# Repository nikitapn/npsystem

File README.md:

# npsystem

A DCS system built around 8-bit AVR micro controller.

## Key Features
- Multi master protocol loosely based on P-NET
- Control units can be uploaded on the fly
- Modify and see propagation of the signal on the running algorithms
- Signal quality bit propagation
- Each micro contoller is an independet unit which can send requests to other devices on the network
- Logic can be tested on virtual controlles
- Controllers supports integration with custom modules via I2C and memory addresses mapping

## Dependencies on Windows
- cygwin https://www.cygwin.com
- make https://gnuwin32.sourceforge.net/packages/make.htm
- perl https://strawberryperl.com
- boost https://www.boost.org/
- leveldb https://github.com/google/leveldb
- scintilla https://www.scintilla.org/SciTEDownload.html
- wtl https://wtl.sourceforge.io/
- AVR toolchain https://www.microchip.com/en-us/tools-resources/develop/microchip-studio/gcc-compilers
- avrdude https://www.nongnu.org/avrdude

## Pictures

<p align="center">
  <b>How it looks</b>
  
  <b>Structural Diagram</b>
  
</p>

## TODO
- [ ] A proper compiler based on LLVM, maybe? With a support for ST language and quality bit propagation.
- [ ] Probably need to remove bit values. It's hard to deal with.
- [ ] Sort dependencies and load all algorithm at once.
- [ ] Add more tests.
- [ ] Add another more powerfull MC, maybe SBP based on Linux (probably a driver will be required for the protocol).
- [ ] Add more FBD blocks (structured text block, etc...).
- [ ] Add SFC language support

## References
1. [MAX3082 Transcievers [PDF]](https://www.analog.com/media/jp/technical-documentation/data-sheets/1522.pdf)
2. [Detection of RS-485 signal loss [PDF]](https://www.ti.com/lit/an/slyt257/slyt257.pdf?ts=1746389303529&ref_url=https%253A%252F%252Fwww.google.com%252F)
3. [P-NET [PDF]](https://www.p-net.org/old/download/mctext.pdf)

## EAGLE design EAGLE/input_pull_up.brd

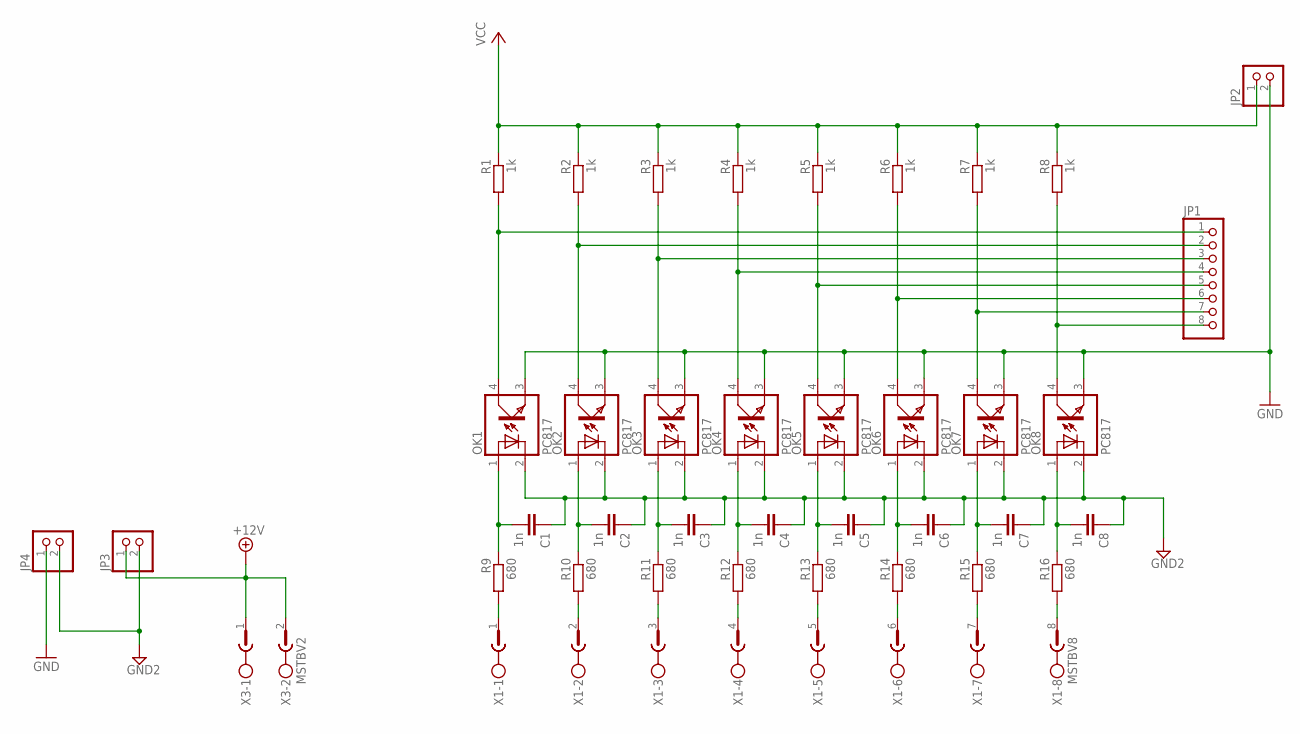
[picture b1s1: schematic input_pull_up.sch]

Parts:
C1, C2, C3, C4, C5, C6, C7, C8: 1n; C050-025X075
JP1: PINHD-1X8; 1X08
JP2, JP3, JP4: PINHD-1X2; 1X02
OK1, OK2, OK3, OK4, OK5, OK6, OK7, OK8: PC817; DIL04
R1, R2, R3, R4, R5, R6, R7, R8: 1k; 0204/7
R9, R10, R11, R12, R13, R14, R15, R16: 680; 0204/7
X1: MSTBV8
X3: MSTBV2

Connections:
+12V: JP3.1, X3.1, X3.2
GND: JP2.2, JP4.1, OK1.3 (EMIT), OK2.3 (EMIT), OK3.3 (EMIT), OK4.3 (EMIT), OK5.3 (EMIT), OK6.3 (EMIT), OK7.3 (EMIT), OK8.3 (EMIT)
GND2: C1.1, C2.1, C3.1, C4.1, C5.1, C6.1, C7.1, C8.1, JP3.2, JP4.2, OK1.2 (C), OK2.2 (C), OK3.2 (C), OK4.2 (C), OK5.2 (C), OK6.2 (C), OK7.2 (C), OK8.2 (C)
unnamed: JP1.1, OK1.4 (COL), R1.2
unnamed: JP1.2, OK2.4 (COL), R2.2
unnamed: JP1.3, OK3.4 (COL), R3.2
unnamed: JP1.4, OK4.4 (COL), R4.2
unnamed: JP1.5, OK5.4 (COL), R5.2
unnamed: JP1.6, OK6.4 (COL), R6.2
unnamed: JP1.7, OK7.4 (COL), R7.2
unnamed: JP1.8, OK8.4 (COL), R8.2
unnamed: R9.2, X1.1
unnamed: R10.2, X1.2
unnamed: R11.2, X1.3
unnamed: R12.2, X1.4
unnamed: R13.2, X1.5
unnamed: R14.2, X1.6
unnamed: R15.2, X1.7
unnamed: R16.2, X1.8
unnamed: C1.2, OK1.1 (A), R9.1
unnamed: C2.2, OK2.1 (A), R10.1
unnamed: C3.2, OK3.1 (A), R11.1
unnamed: C4.2, OK4.1 (A), R12.1
unnamed: C5.2, OK5.1 (A), R13.1
unnamed: C6.2, OK6.1 (A), R14.1
unnamed: C7.2, OK7.1 (A), R15.1
unnamed: C8.2, OK8.1 (A), R16.1
VCC: JP2.1, R1.1, R2.1, R3.1, R4.1, R5.1, R6.1, R7.1, R8.1

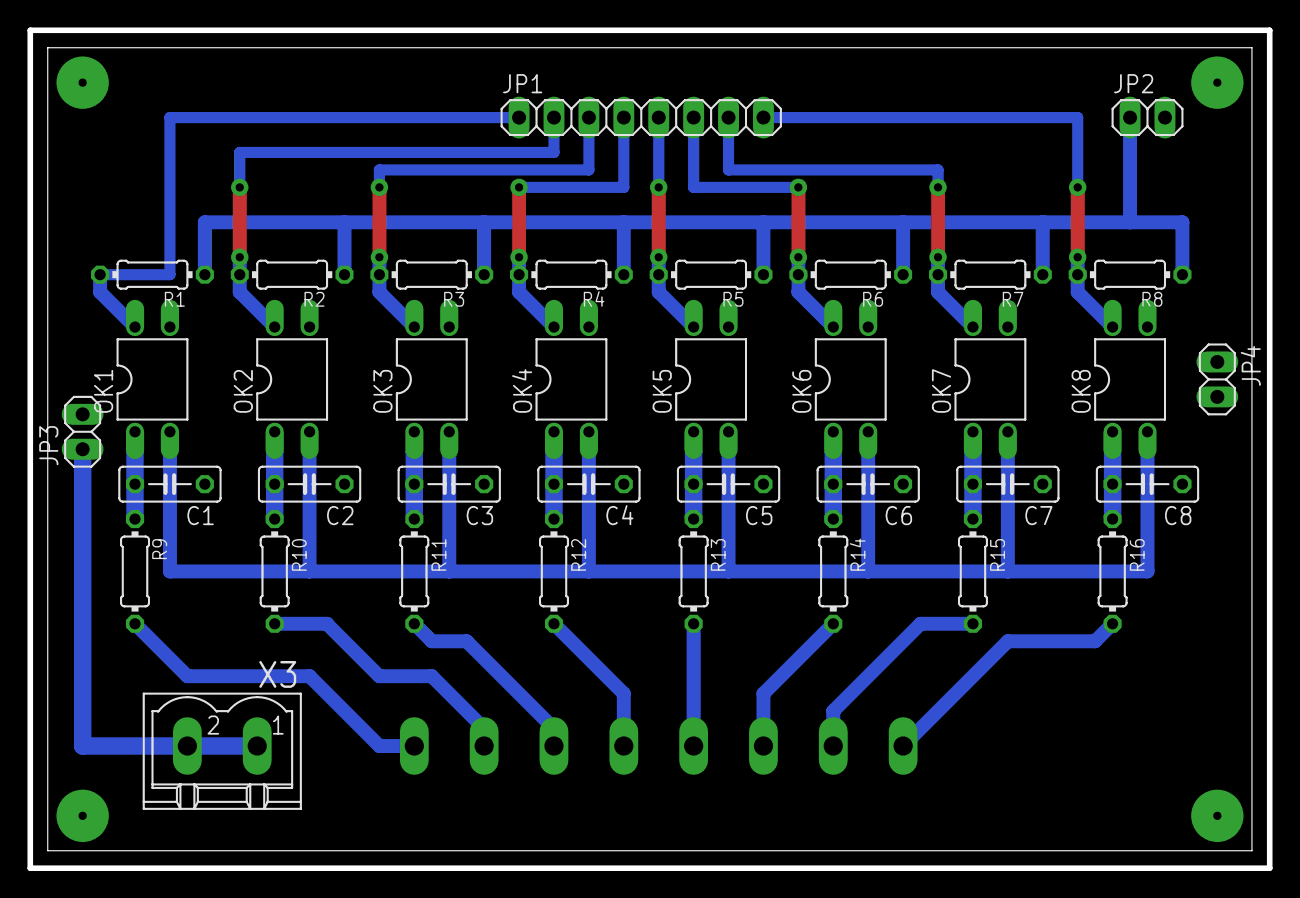
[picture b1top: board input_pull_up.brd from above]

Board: 2 copper layers, 90.2 x 61.0 mm, 38 parts (1 on the bottom side), 28 nets.

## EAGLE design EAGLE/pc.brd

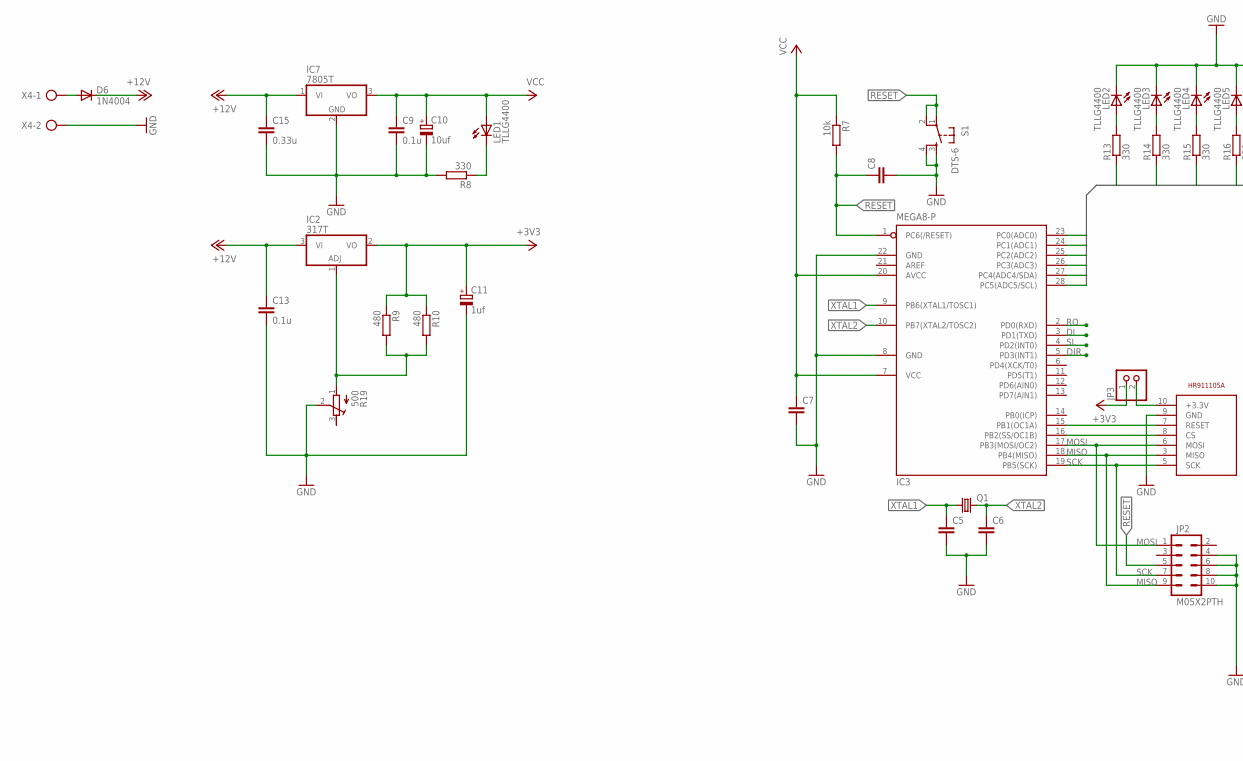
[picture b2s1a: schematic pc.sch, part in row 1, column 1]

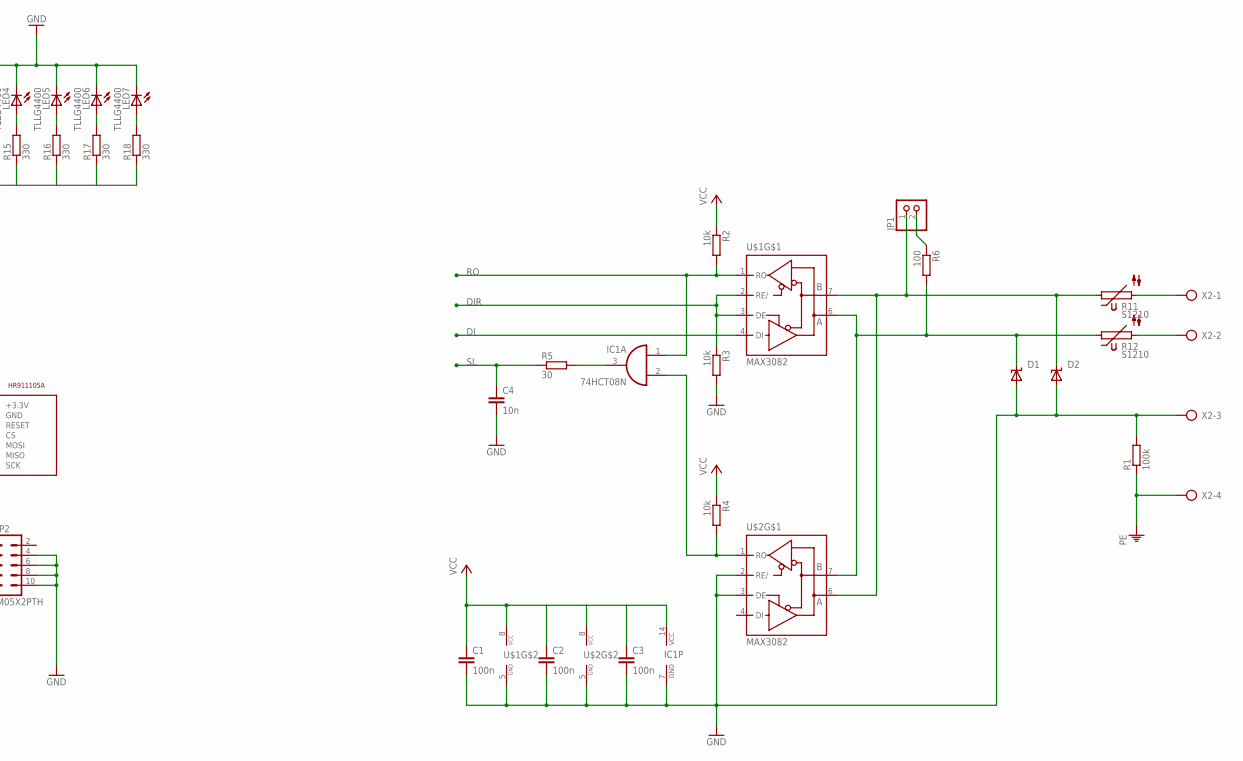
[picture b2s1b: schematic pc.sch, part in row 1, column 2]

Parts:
C1, C2, C3: 100n; C050-035X075
C4: 10n; C050-035X075
C5, C6: C-EU050-024X044; C050-024X044
C7, C8: C-EU050-025X075; C050-025X075
C9, C13: 0.1u; C025-024X044
C10: 10uf; E2-4
C11: 1uf; E2-4
C15: 0.33u; C025-024X044
D1, D2: SUPPRESSOR-SMBJ; SMBJ
D6: 1N4004; DO41-10
IC1: 74HCT08N; DIL14
IC2: 317T; TO220H
IC3: MEGA8-P; DIL28-3
IC7: 7805T; TO220H
JP1, JP3: PINHD-1X2; 1X02
JP2: M05X2PTH; AVR_ICSP
LED1, LED2, LED3, LED4, LED5, LED6, LED7: TLLG4400; LED3MM
Q1: CRYSTALHC49U70; HC49U70
R1: 100k; 0204/7
R2, R3, R4, R7: 10k; 0204/7
R5: 30; 0207/10
R6: 100; 0204/7
R8, R13, R14, R15, R16, R17, R18: 330; 0204/7
R9, R10: 480; 0204/7
R11, R12: S1210
R19: 500; RTRIM64W
S1: DTS-6
U$1, U$2: MAX3082; DIL08
U$3: HR911105A
X2: AK500/4
X4: AK500/2-H

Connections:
+3V3: C11.+, IC2.2 (VO), JP3.1, R9.1, R10.1
+12V: C13.1, C15.1, D6.C, IC2.3 (VI), IC7.1 (VI)
DI: IC3.3 (PD1(TXD)), U$1.4 (DI)
DIR: IC3.5 (PD3(INT1)), R3.1, U$1.2 (RE/), U$1.3 (DE)
GND: C1.2, C2.2, C3.2, C4.2, C5.2, C6.2, C7.2, C8.2, C9.2, C10.-, C11.-, C13.2, C15.2, D1.A, D2.A, IC1.7 (GND), IC3.8 (GND), IC3.22 (GND), IC7.2 (GND), JP2.4, JP2.6, JP2.8, JP2.10, LED2.K (C), LED3.K (C), LED4.K (C), LED5.K (C), LED6.K (C), LED7.K (C), R1.2, R3.2, R8.2, R19.2 (S), S1.3, S1.4, U$1.5 (GND), U$2.2 (RE/), U$2.3 (DE), U$2.5 (GND), U$3.9 (GND), X2.3, X4.2
LED0: IC3.23 (PC0(ADC0)), R13.1
LED1: IC3.24 (PC1(ADC1)), R14.1
LED2: IC3.25 (PC2(ADC2)), R15.1
LED3: IC3.26 (PC3(ADC3)), R16.1
LED4: IC3.27 (PC4(ADC4/SDA)), R17.1
LED5: IC3.28 (PC5(ADC5/SCL)), R18.1
MISO: IC3.18 (PB4(MISO)), JP2.9, U$3.3 (MISO)
MOSI: IC3.17 (PB3(MOSI/OC2)), JP2.1, U$3.6 (MOSI)
unnamed: IC2.1 (ADJ), R9.2, R10.2, R19.1 (A)
unnamed: D1.C, R6.2, R12.1, U$1.6 (A), U$2.7 (B)
unnamed: IC1.2 (I1), R4.2, U$2.1 (RO)
unnamed: LED1.K (C), R8.1
unnamed: IC3.16 (PB2(SS/OC1B)), U$3.8 (CS)
unnamed: LED2.A, R13.2
unnamed: IC1.3 (O), R5.2
unnamed: JP1.2, R6.1
unnamed: R11.2, X2.1
unnamed: D2.C, JP1.1, R11.1, U$1.7 (B), U$2.6 (A)
unnamed: R12.2, X2.2
unnamed: LED3.A, R14.2
unnamed: LED4.A, R15.2
unnamed: LED5.A, R16.2
unnamed: LED6.A, R17.2
unnamed: LED7.A, R18.2
unnamed: IC3.15 (PB1(OC1A)), U$3.7 (RESET)
unnamed: JP3.2, U$3.10 (+3.3V)
unnamed: D6.A, X4.1
PE: R1.1, X2.4
RESET: C8.1, IC3.1 (PC6(/RESET)), JP2.5, R7.2, S1.1, S1.2
RO: IC1.1 (I0), IC3.2 (PD0(RXD)), R2.2, U$1.1 (RO)
SCK: IC3.19 (PB5(SCK)), JP2.7, U$3.5 (SCK)
SL: C4.1, IC3.4 (PD2(INT0)), R5.1
VCC: C1.1, C2.1, C3.1, C7.1, C9.1, C10.+, IC1.14 (VCC), IC3.7 (VCC), IC3.20 (AVCC), IC7.3 (VO), LED1.A, R2.1, R4.1, R7.1, U$1.8 (VCC), U$2.8 (VCC)
XTAL1: C5.1, IC3.9 (PB6(XTAL1/TOSC1)), Q1.1
XTAL2: C6.1, IC3.10 (PB7(XTAL2/TOSC2)), Q1.2

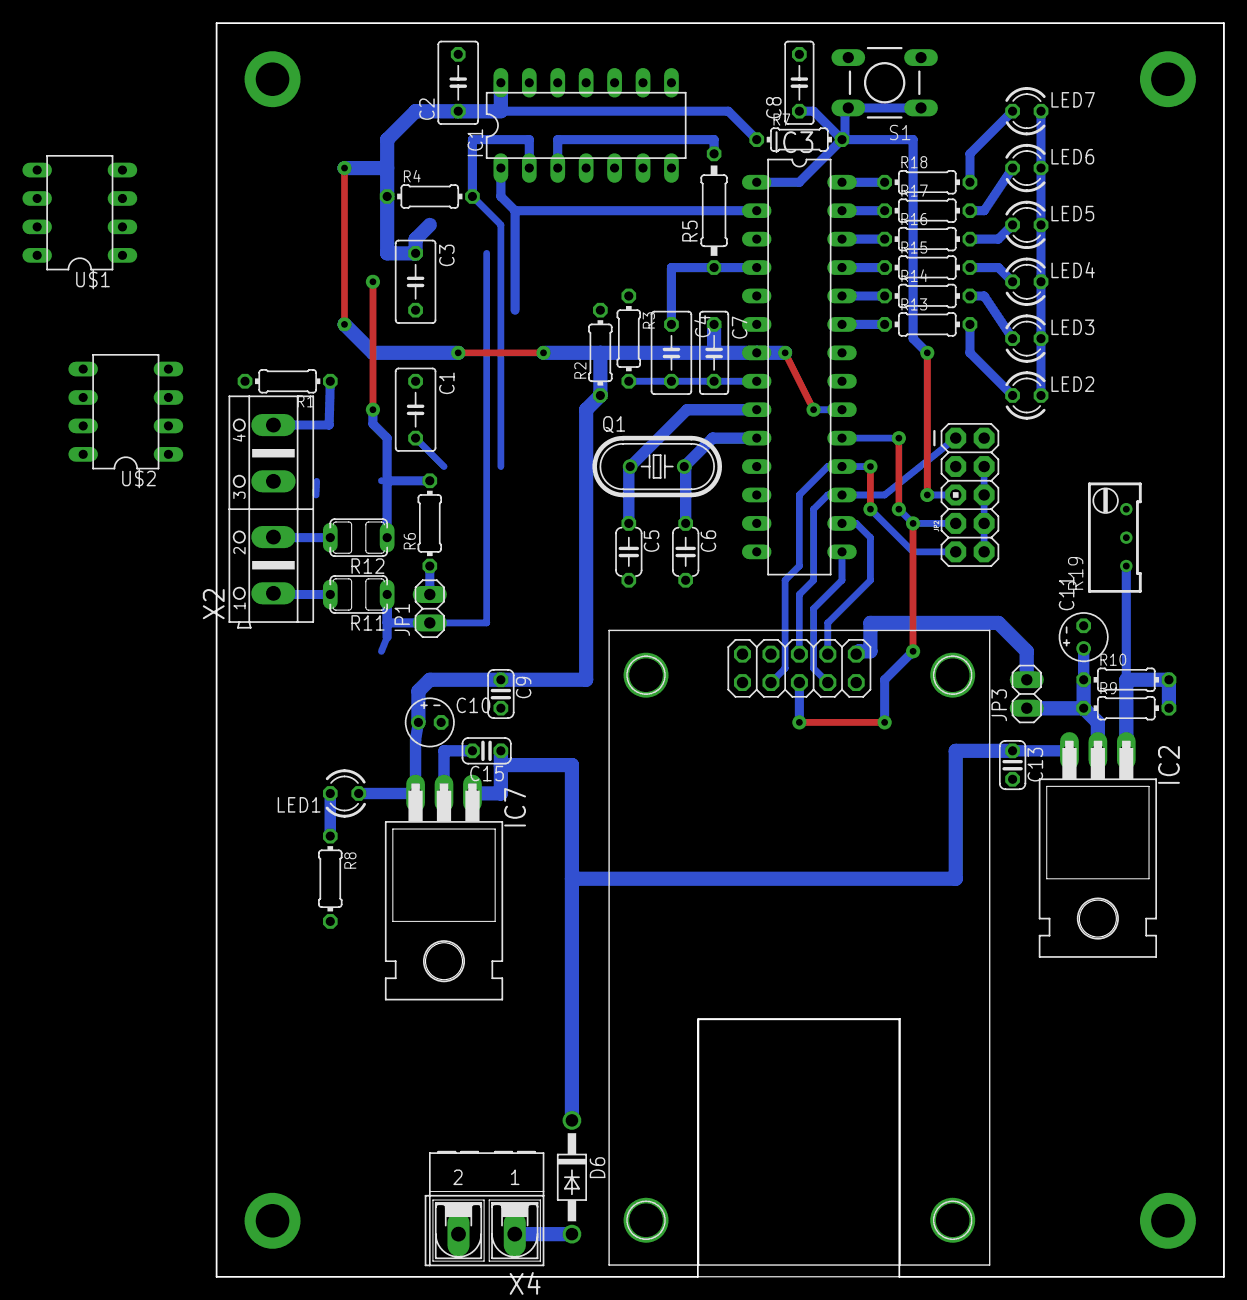
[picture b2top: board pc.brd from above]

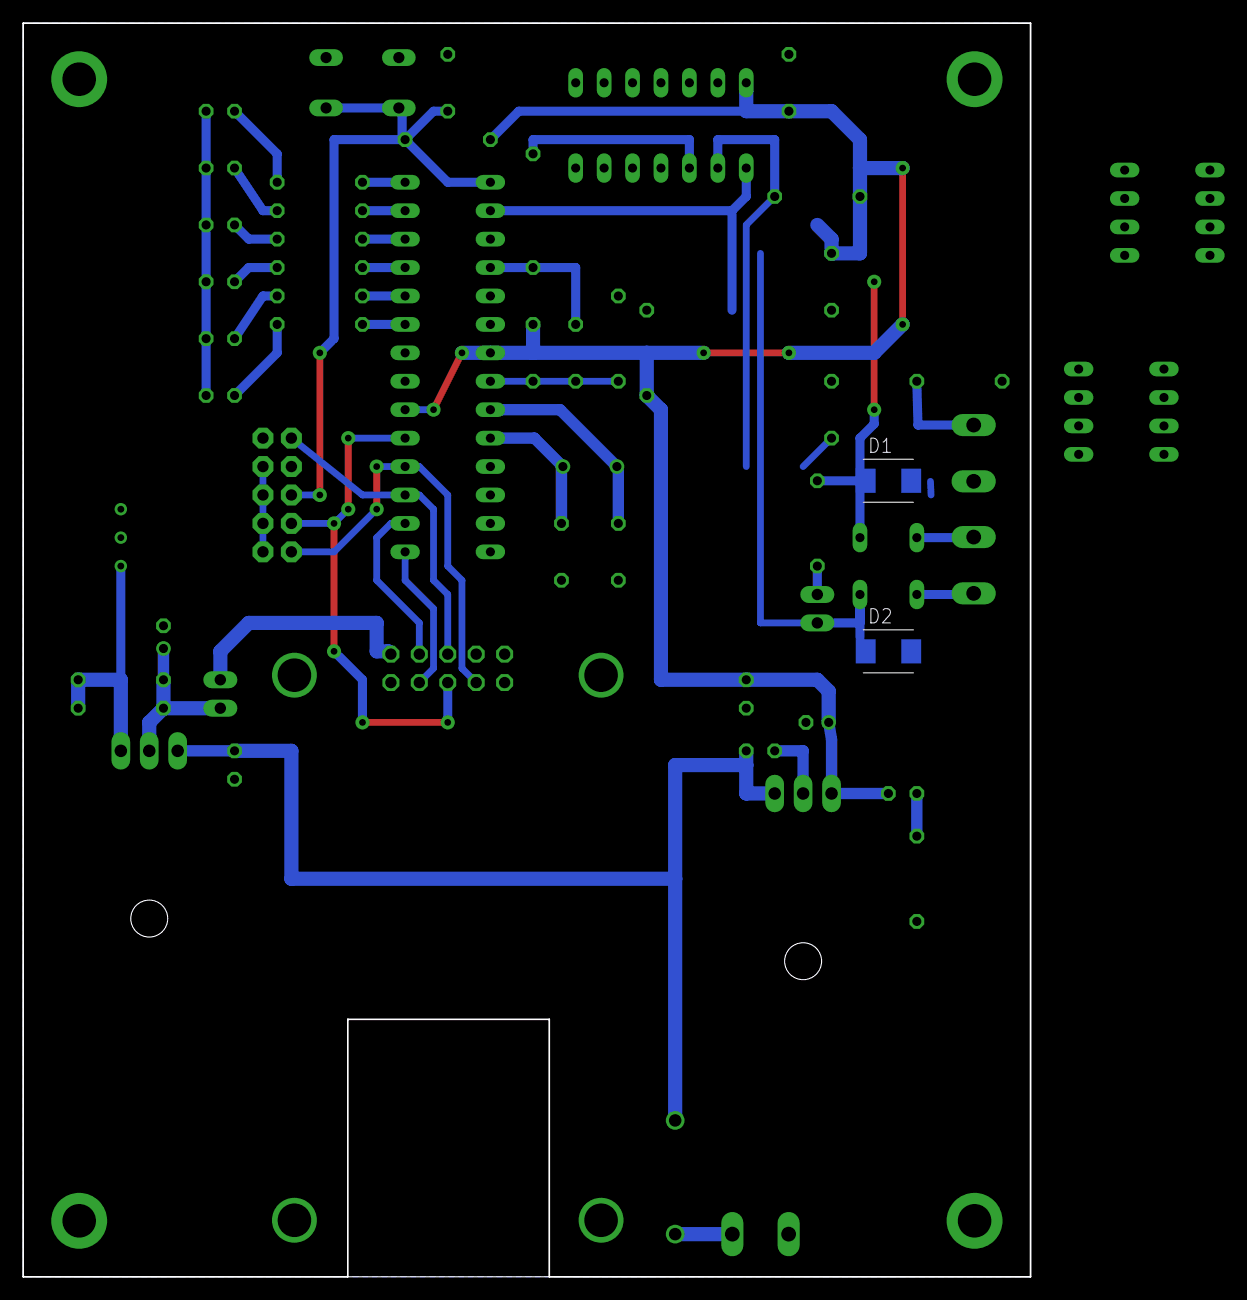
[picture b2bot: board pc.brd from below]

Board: 2 copper layers, 90.0 x 112.0 mm, 56 parts (2 on the bottom side), 40 nets.

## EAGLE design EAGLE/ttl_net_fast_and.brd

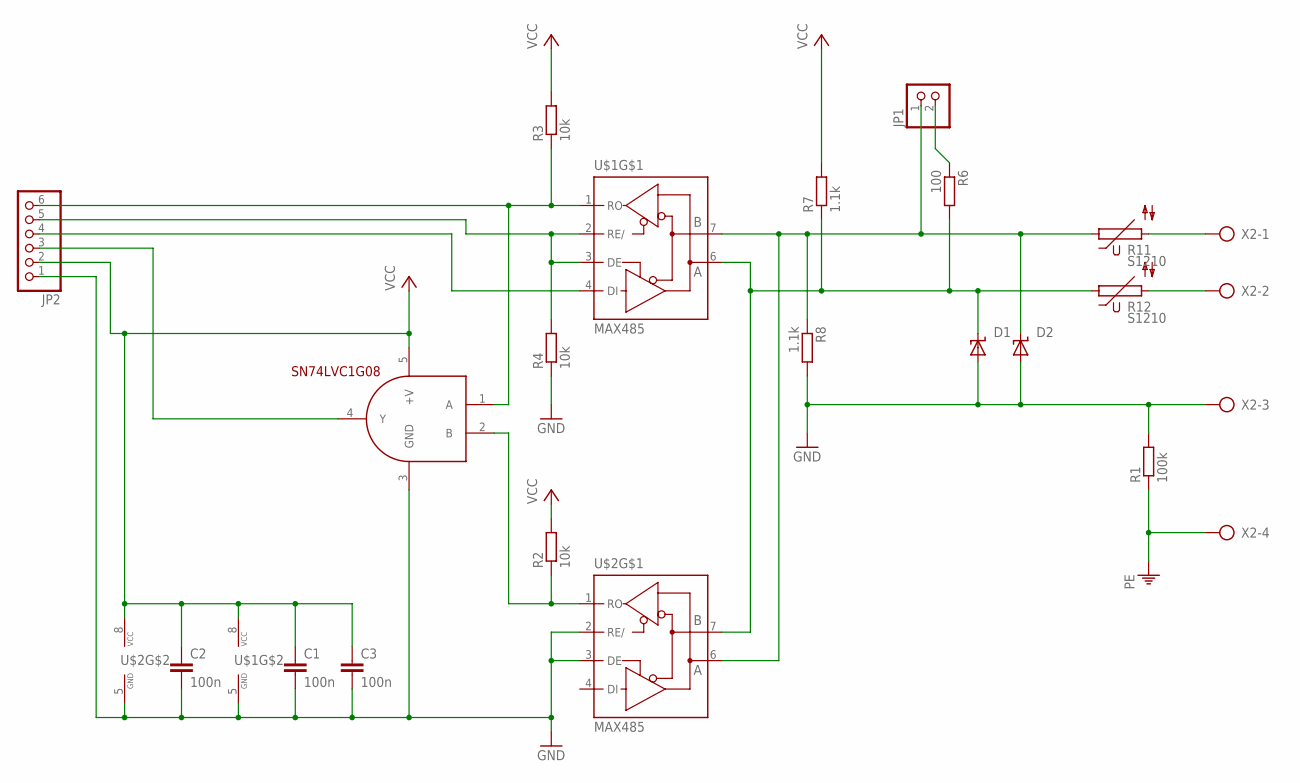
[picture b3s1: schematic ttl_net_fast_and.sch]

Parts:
C1, C2: 100n; C050-035X075
C3: 100n; C1206
D1, D2: SUPPRESSOR-SMBJ; SMBJ
JP1: PINHD-1X2; 1X02
JP2: PINHD-1X6; 1X06
R1: 100k; 0204/7
R2, R3, R4: 10k; R1206
R6: 100; 0204/7
R7, R8: 1.1k; 0204/7
R11, R12: S1210
U$1, U$2: MAX485; DIL08
U$3: SN74LVC1G08; SOT23-5
X2: AK500/4

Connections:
GND: C1.2, C2.2, C3.2, D1.A, D2.A, JP2.1, R1.2, R4.1, R8.2, U$1.5 (GND), U$2.2 (RE/), U$2.3 (DE), U$2.5 (GND), U$3.3 (GND), X2.3
unnamed: D1.C, R6.2, R7.1, R12.1, U$1.6 (A), U$2.7 (B)
unnamed: R2.1, U$2.1 (RO), U$3.2 (B)
unnamed: JP2.4, U$1.4 (DI)
unnamed: JP2.3, U$3.4 (Y)
unnamed: JP2.6, R3.1, U$1.1 (RO), U$3.1 (A)
unnamed: JP2.5, R4.2, U$1.2 (RE/), U$1.3 (DE)
unnamed: JP1.2, R6.1
unnamed: R11.2, X2.1
unnamed: D2.C, JP1.1, R8.1, R11.1, U$1.7 (B), U$2.6 (A)
unnamed: R12.2, X2.2
PE: R1.1, X2.4
VCC: C1.1, C2.1, C3.1, JP2.2, R2.2, R3.2, R7.2, U$1.8 (VCC), U$2.8 (VCC), U$3.5 (+V)

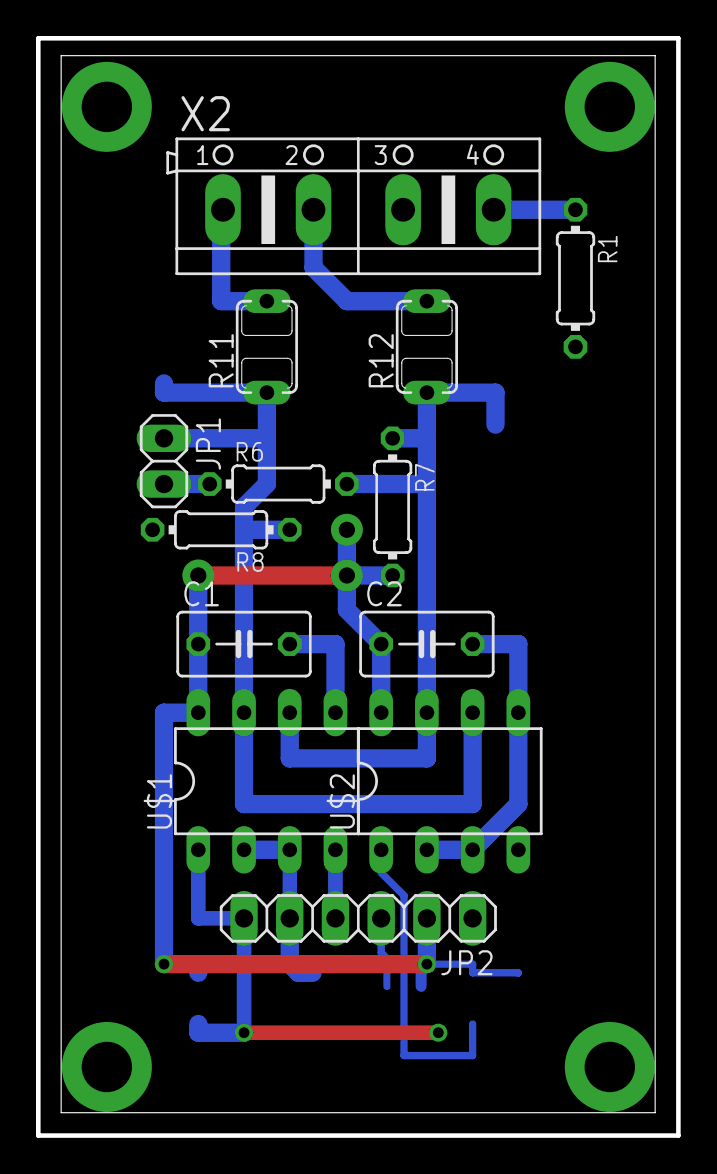
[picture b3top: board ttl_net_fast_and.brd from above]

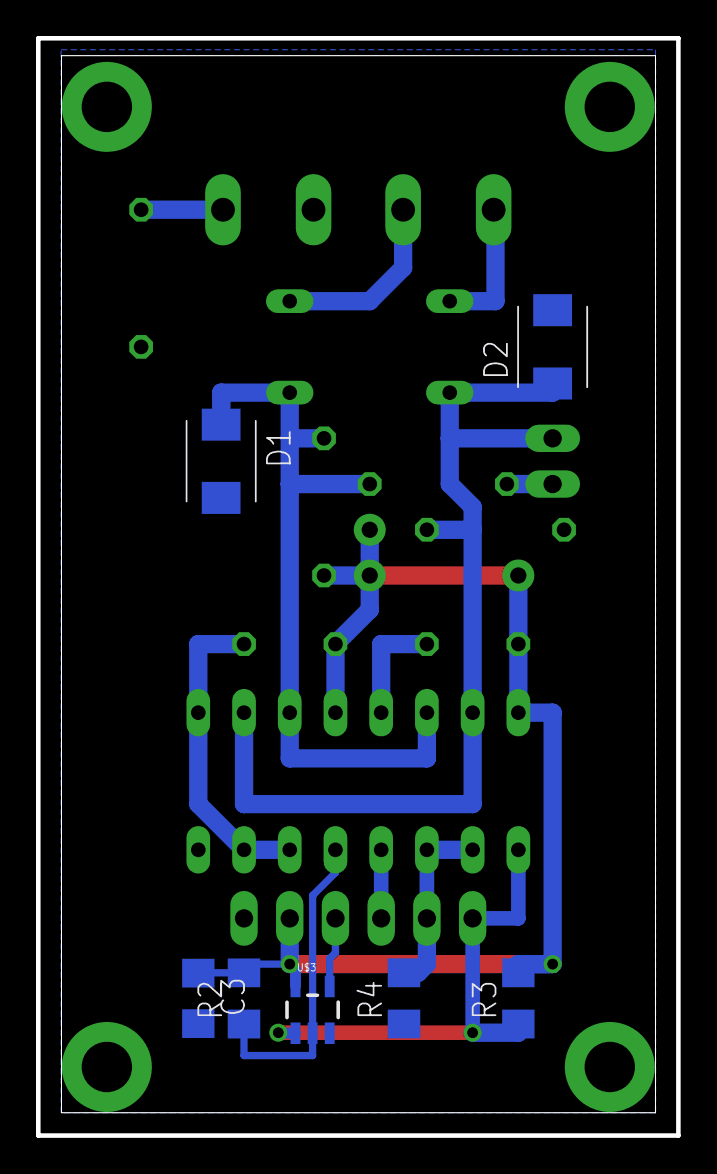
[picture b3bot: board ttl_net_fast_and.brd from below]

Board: 2 copper layers, 35.6 x 61.0 mm, 20 parts (7 on the bottom side), 13 nets.

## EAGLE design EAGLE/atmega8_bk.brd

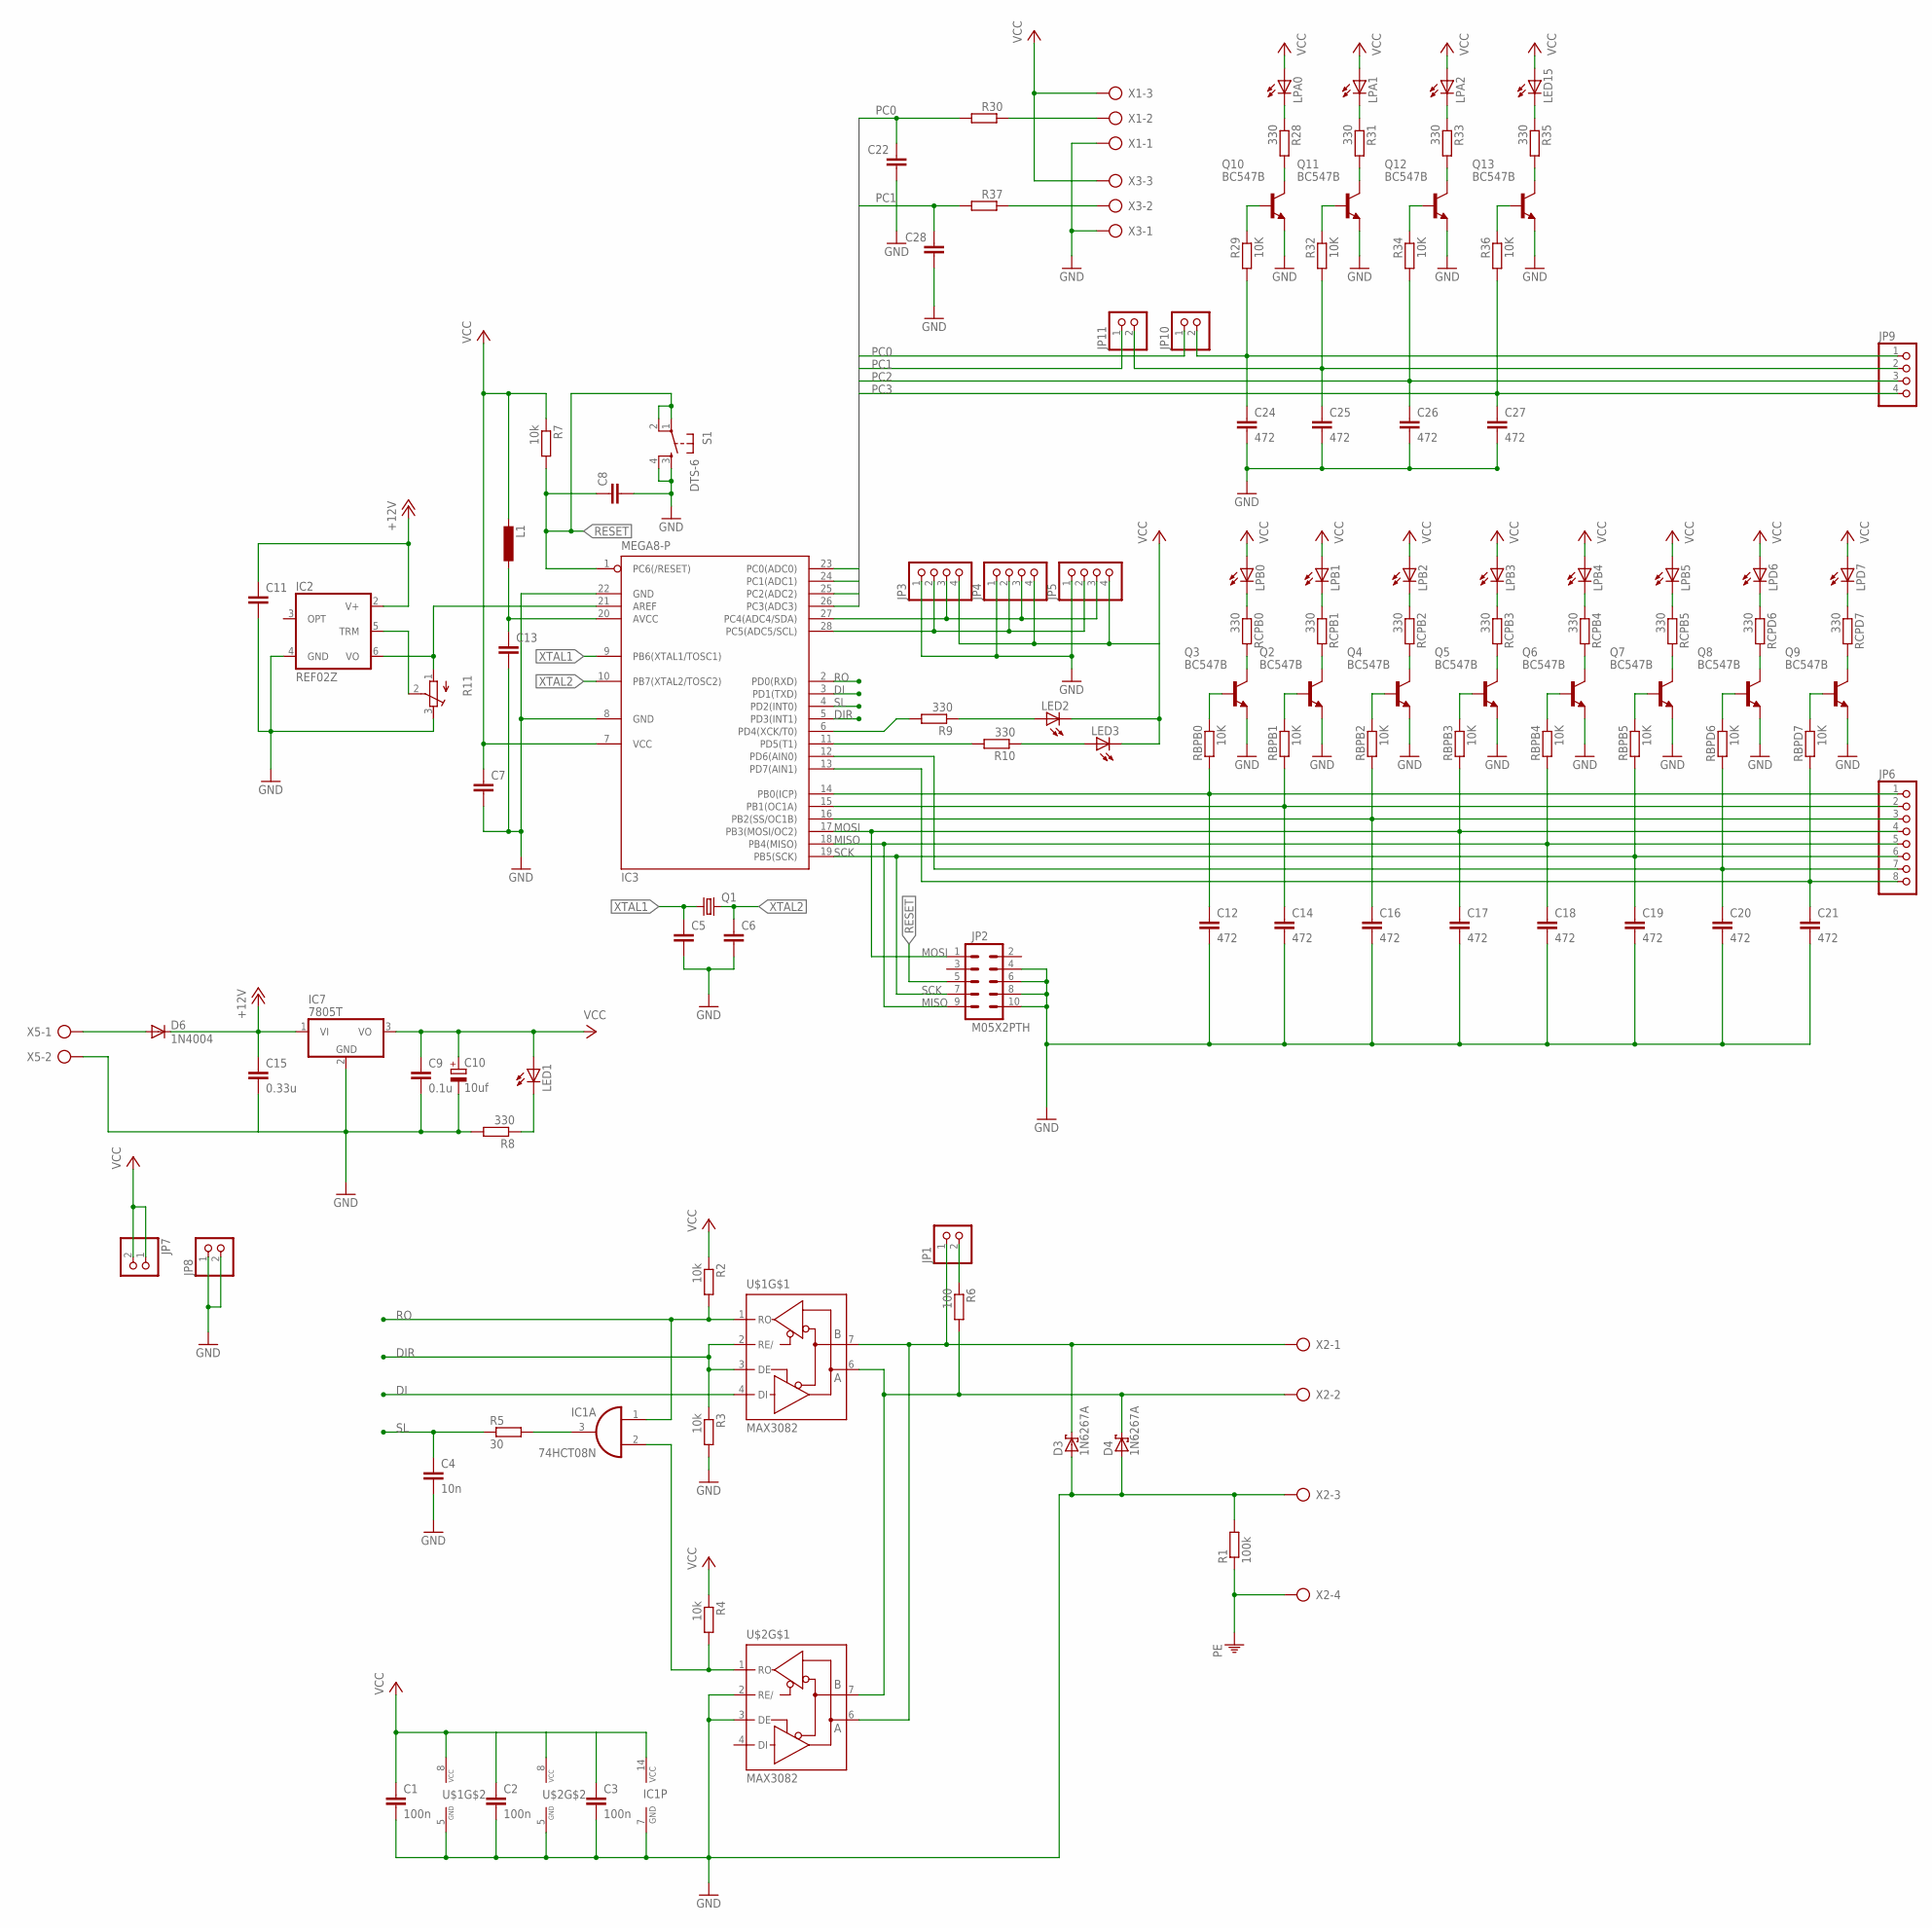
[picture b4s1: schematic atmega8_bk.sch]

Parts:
C1, C2, C3: 100n; C050-035X075
C4: 10n; C050-035X075
C5, C6: C-EU050-024X044; C050-024X044
C7, C8, C11, C13, C22, C28: C-EU050-025X075; C050-025X075
C9: 0.1u; C025-024X044
C10: 10uf; E2-4
C12, C14, C16, C17, C18, C19, C20, C21, C24, C25, C26, C27: 472; C050-024X044
C15: 0.33u; C025-024X044
D3, D4: 1N6267A; C4111-15
D6: 1N4004; DO41-10
IC1: 74HCT08N; DIL14
IC2: REF02Z; DIL08
IC3: MEGA8-P; DIL28-3
IC7: 7805T; TO220H
JP1, JP7, JP8, JP10, JP11: PINHD-1X2; 1X02
JP2: M05X2PTH; AVR_ICSP
JP3, JP4, JP5, JP9: PINHD-1X4; 1X04
JP6: PINHD-1X8; 1X08
L1: L-EU0207/12; 0207/12
LED1, LED2, LED3, LED15: LED3MM
LPA0, LPA1, LPA2: LED3MM
LPB0, LPB1, LPB2, LPB3, LPB4, LPB5: LED3MM
LPD6, LPD7: LED3MM
Q1: CRYSTALHC49U70; HC49U70
Q2, Q3, Q4, Q5, Q6, Q7, Q8, Q9, Q10, Q11, Q12, Q13: BC547B; TO92
R1: 100k; 0204/7
R2, R3, R4, R7: 10k; 0204/7
R5: 30; 0207/10
R6: 100; 0204/7
R8, R9, R10, R28, R31, R33, R35: 330; 0204/7
R11: R-TRIMM64W; RTRIM64W
R29, R32, R34, R36: 10K; 0204/7
R30, R37: R-EU_0204/7; 0204/7
RBPB0, RBPB1, RBPB2, RBPB3, RBPB4, RBPB5: 10K; 0204/7
RBPD6, RBPD7: 10K; 0204/7
RCPB0, RCPB1, RCPB2, RCPB3, RCPB4, RCPB5: 330; 0204/7
RCPD6, RCPD7: 330; 0204/7
S1: DTS-6
U$1, U$2: MAX3082; DIL08
X1, X3: AK500/3
X2: AK500/4
X5: AK500/2

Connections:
+12V: C11.1, C15.1, D6.C, IC2.2 (V+), IC7.1 (VI)
AREF: IC2.6 (VO), IC3.21 (AREF), R11.1 (A)
DI: IC3.3 (PD1(TXD)), U$1.4 (DI)
DIR: IC3.5 (PD3(INT1)), R3.1, U$1.2 (RE/), U$1.3 (DE)
GND: C1.2, C2.2, C3.2, C4.2, C5.2, C6.2, C7.2, C8.2, C9.2, C10.-, C11.2, C12.2, C13.2, C14.2, C15.2, C16.2, C17.2, C18.2, C19.2, C20.2, C21.2, C22.2, C24.2, C25.2, C26.2, C27.2, C28.2, D3.A, D4.A, IC1.7 (GND), IC2.4 (GND), IC3.8 (GND), IC3.22 (GND), IC7.2 (GND), JP2.4, JP2.6, JP2.8, JP2.10, JP3.1, JP4.1, JP5.1, JP8.1, JP8.2, Q2.1 (E), Q3.1 (E), Q4.1 (E), Q5.1 (E), Q6.1 (E), Q7.1 (E), Q8.1 (E), Q9.1 (E), Q10.1 (E), Q11.1 (E), Q12.1 (E), Q13.1 (E), R1.2, R3.2, R8.2, R11.3 (E), S1.3, S1.4, U$1.5 (GND), U$2.2 (RE/), U$2.3 (DE), U$2.5 (GND), X1.1, X2.3, X3.1, X5.2
LPA3: LED15.K (C), R35.1
MISO: C18.1, IC3.18 (PB4(MISO)), JP2.9, JP6.5, RBPB4.2
MOSI: C17.1, IC3.17 (PB3(MOSI/OC2)), JP2.1, JP6.4, RBPB3.2
unnamed: LPB0.K (C), RCPB0.1
unnamed: D4.C, R6.2, U$1.6 (A), U$2.7 (B), X2.2
unnamed: IC1.2 (I1), R4.2, U$2.1 (RO)
unnamed: LED1.K (C), R8.1
unnamed: LED3.A, R10.1
unnamed: IC2.5 (TRM), R11.2 (S)
unnamed: IC1.3 (O), R5.2
unnamed: JP1.2, R6.1
unnamed: D3.C, JP1.1, U$1.7 (B), U$2.6 (A), X2.1
unnamed: C13.1, IC3.20 (AVCC), L1.1
unnamed: Q3.3 (C), RCPB0.2
unnamed: Q3.2 (B), RBPB0.1
unnamed: C12.1, IC3.14 (PB0(ICP)), JP6.1, RBPB0.2
unnamed: C14.1, IC3.15 (PB1(OC1A)), JP6.2, RBPB1.2
unnamed: C16.1, IC3.16 (PB2(SS/OC1B)), JP6.3, RBPB2.2
unnamed: C20.1, IC3.12 (PD6(AIN0)), JP6.7, RBPD6.2
unnamed: C21.1, IC3.13 (PD7(AIN1)), JP6.8, RBPD7.2
unnamed: IC3.28 (PC5(ADC5/SCL)), JP3.2, JP4.2, JP5.2
unnamed: D6.A, X5.1
unnamed: Q2.3 (C), RCPB1.2
unnamed: Q2.2 (B), RBPB1.1
unnamed: IC3.27 (PC4(ADC4/SDA)), JP3.3, JP4.3, JP5.3
unnamed: IC3.6 (PD4(XCK/T0)), R9.2
unnamed: IC3.11 (PD5(T1)), R10.2
unnamed: LPB1.K (C), RCPB1.1
unnamed: LED2.A, R9.1
unnamed: Q4.3 (C), RCPB2.2
unnamed: Q4.2 (B), RBPB2.1
unnamed: LPB2.K (C), RCPB2.1
unnamed: Q5.3 (C), RCPB3.2
unnamed: Q5.2 (B), RBPB3.1
unnamed: LPB3.K (C), RCPB3.1
unnamed: Q6.3 (C), RCPB4.2
unnamed: Q6.2 (B), RBPB4.1
unnamed: LPB4.K (C), RCPB4.1
unnamed: Q7.3 (C), RCPB5.2
unnamed: Q7.2 (B), RBPB5.1
unnamed: LPB5.K (C), RCPB5.1
unnamed: Q8.3 (C), RCPD6.2
unnamed: Q8.2 (B), RBPD6.1
unnamed: LPD6.K (C), RCPD6.1
unnamed: Q9.3 (C), RCPD7.2
unnamed: Q9.2 (B), RBPD7.1
unnamed: LPD7.K (C), RCPD7.1
unnamed: R30.1, X1.2
unnamed: Q10.3 (C), R28.2
unnamed: Q10.2 (B), R29.1
unnamed: C24.1, JP9.1, JP10.2, R29.2
unnamed: C25.1, JP9.2, JP11.2, R32.2
unnamed: LPA0.K (C), R28.1
unnamed: Q11.3 (C), R31.2
unnamed: Q11.2 (B), R32.1
unnamed: LPA1.K (C), R31.1
unnamed: Q12.3 (C), R33.2
unnamed: Q12.2 (B), R34.1
unnamed: LPA2.K (C), R33.1
unnamed: Q13.3 (C), R35.2
unnamed: Q13.2 (B), R36.1
unnamed: R37.1, X3.2
PC0: C22.1, IC3.23 (PC0(ADC0)), JP10.1, R30.2
PC1: C28.1, IC3.24 (PC1(ADC1)), JP11.1, R37.2
PC2: C26.1, IC3.25 (PC2(ADC2)), JP9.3, R34.2
PC3: C27.1, IC3.26 (PC3(ADC3)), JP9.4, R36.2
PE: R1.1, X2.4
RESET: C8.1, IC3.1 (PC6(/RESET)), JP2.5, R7.2, S1.1, S1.2
RO: IC1.1 (I0), IC3.2 (PD0(RXD)), R2.2, U$1.1 (RO)
SCK: C19.1, IC3.19 (PB5(SCK)), JP2.7, JP6.6, RBPB5.2
SL: C4.1, IC3.4 (PD2(INT0)), R5.1
VCC: C1.1, C2.1, C3.1, C7.1, C9.1, C10.+, IC1.14 (VCC), IC3.7 (VCC), IC7.3 (VO), JP3.4, JP4.4, JP5.4, JP7.1, JP7.2, L1.2, LED1.A, LED2.K (C), LED3.K (C), LED15.A, LPA0.A, LPA1.A, LPA2.A, LPB0.A, LPB1.A, LPB2.A, LPB3.A, LPB4.A, LPB5.A, LPD6.A, LPD7.A, R2.1, R4.1, R7.1, U$1.8 (VCC), U$2.8 (VCC), X1.3, X3.3
XTAL1: C5.1, IC3.9 (PB6(XTAL1/TOSC1)), Q1.1
XTAL2: C6.1, IC3.10 (PB7(XTAL2/TOSC2)), Q1.2

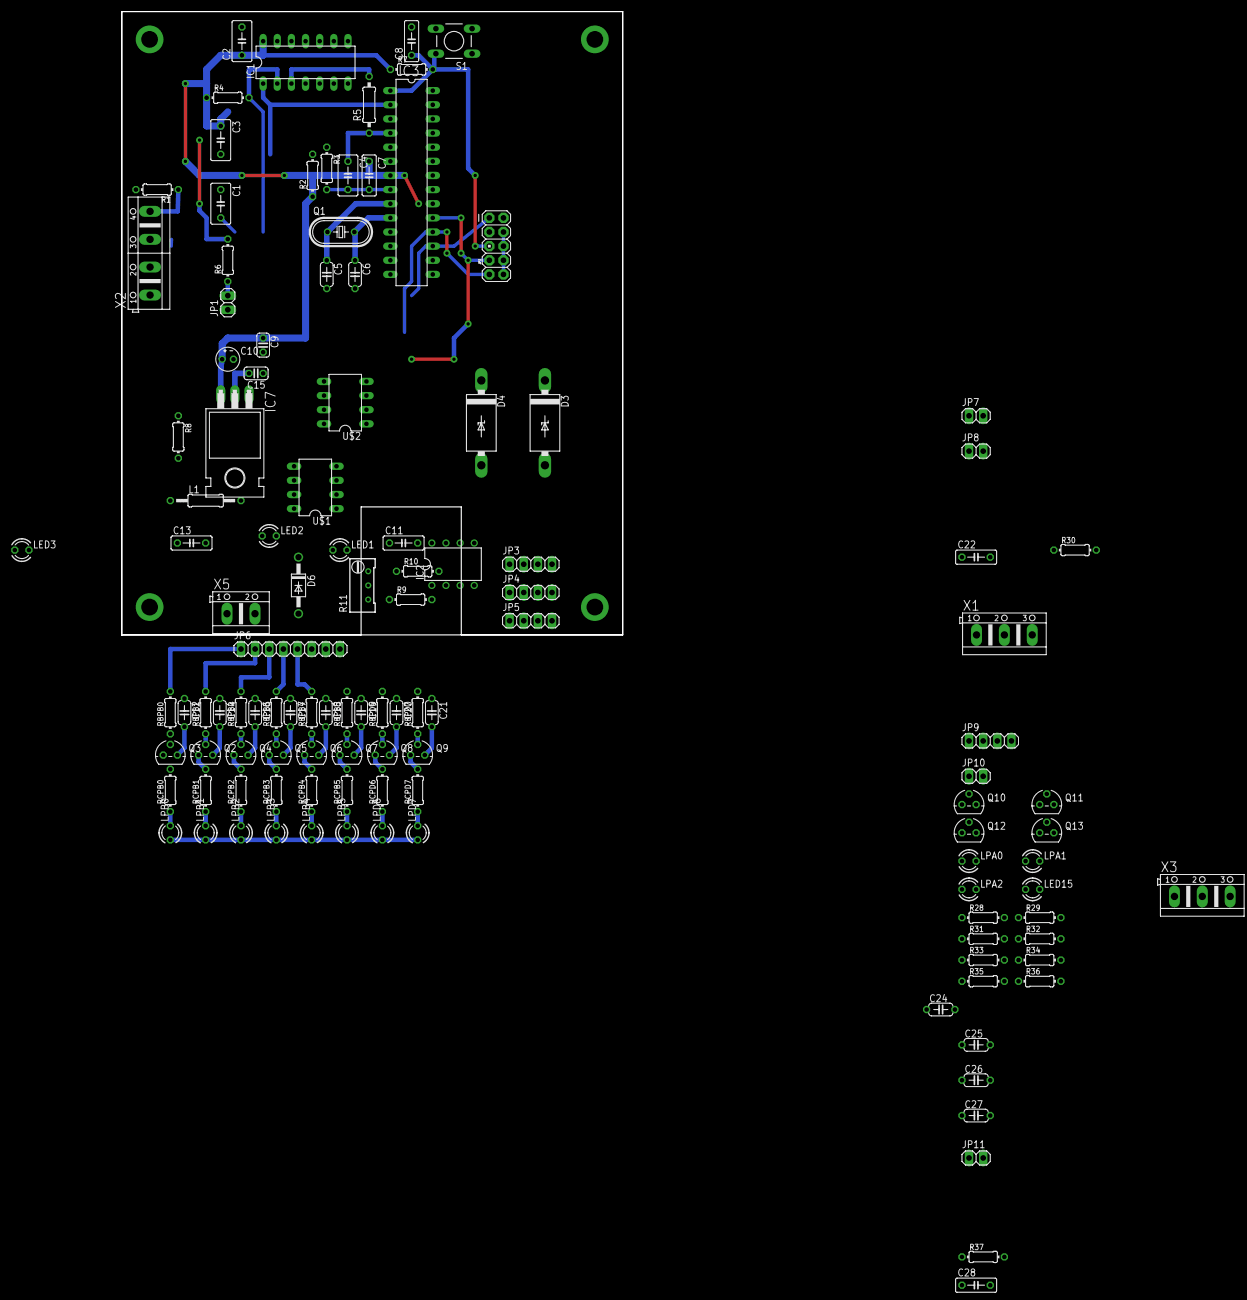
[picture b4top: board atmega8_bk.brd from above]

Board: 2 copper layers, 90.0 x 112.0 mm, 118 parts (0 on the bottom side), 79 nets.

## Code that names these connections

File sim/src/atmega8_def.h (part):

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	static constexpr int DDD7 = 7;

	//static constexpr int PORTD=_SFR_IO8(0x12)
	static constexpr int PD0 = 0;
	static constexpr int PD1 = 1;
	static constexpr int PD2 = 2;
	static constexpr int PD3 = 3;
	static constexpr int PD4 = 4;
	static constexpr int PD5 = 5;
	static constexpr int PD6 = 6;
	static constexpr int PD7 = 7;

	//static constexpr int PINC= _SFR_IO8(0x13)
	static constexpr int PINC0 = 0;
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	static constexpr int DDC6 = 6;

	//static constexpr int PORTC=_SFR_IO8(0x15)
	static constexpr int PC0 = 0;
	static constexpr int PC1 = 1;
	static constexpr int PC2 = 2;
	static constexpr int PC3 = 3;
	static constexpr int PC4 = 4;
	static constexpr int PC5 = 5;
	static constexpr int PC6 = 6;

	//static constexpr int PINB= _SFR_IO8(0x16)
	static constexpr int PINB0 = 0;
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	static constexpr int DDB7 = 7;

	//static constexpr int PORTB=_SFR_IO8(0x18)
	static constexpr int PB0 = 0;
	static constexpr int PB1 = 1;
	static constexpr int PB2 = 2;
	static constexpr int PB3 = 3;
	static constexpr int PB4 = 4;
	static constexpr int PB5 = 5;
	static constexpr int PB6 = 6;
	static constexpr int PB7 = 7;


	/* EEPROM Control Register */
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

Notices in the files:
sim/src/atmega8_def.h:
Copyright (c) 2021-2025, Nikita Pennie <nikitapnn1@gmail.com>
